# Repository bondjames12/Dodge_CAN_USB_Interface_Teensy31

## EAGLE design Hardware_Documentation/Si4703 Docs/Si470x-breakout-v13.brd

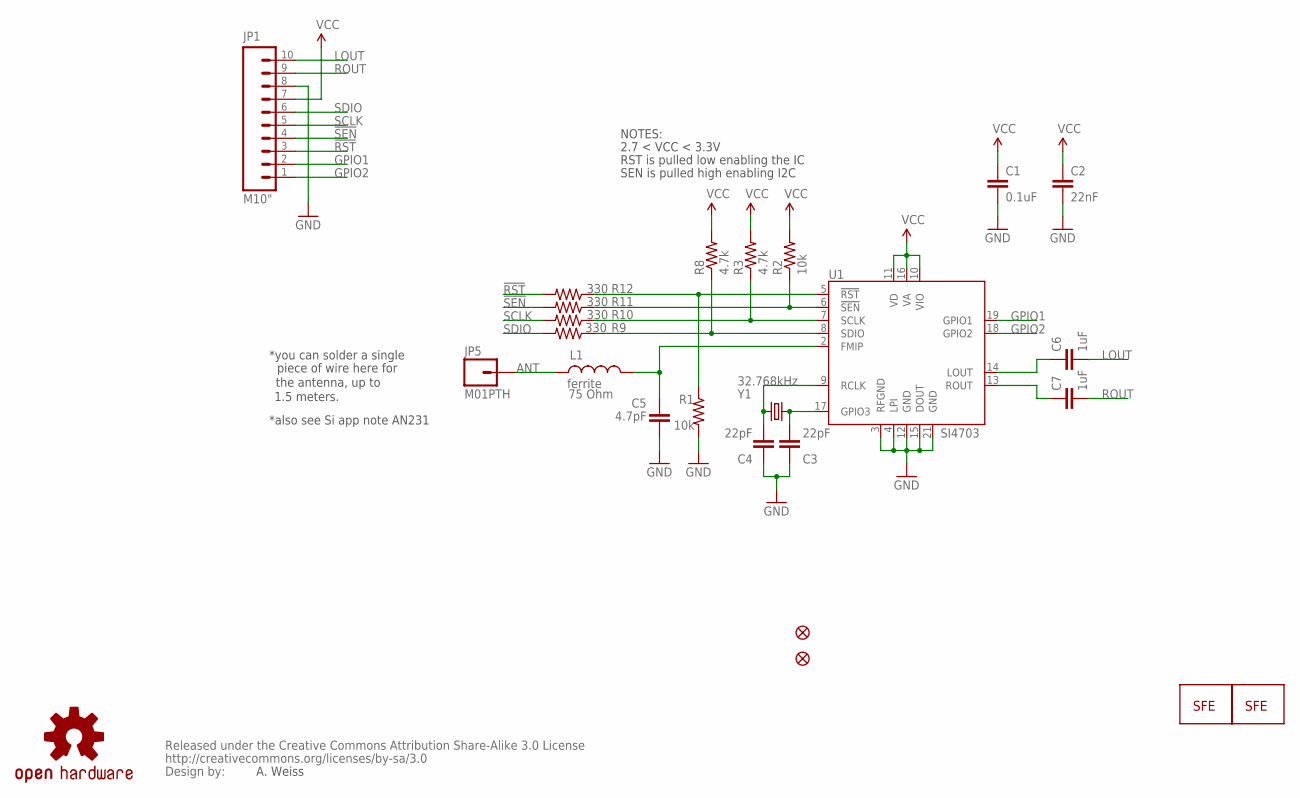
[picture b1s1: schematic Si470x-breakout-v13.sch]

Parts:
C1: 0.1uF; 0402-CAP
C2: 22nF; 0402-CAP
C3, C4: 22pF; 0402-CAP
C5: 4.7pF; 0402-CAP
C6, C7: 1uF; 0402-CAP
JP1: M10"; 1X10
JP2: LOGO-SFENW2; SFE-NEW-WEB
JP3: LOGO-SFESK; SFE-LOGO-FLAME
JP4, JP6: FIDUCIALUFIDUCIAL; MICRO-FIDUCIAL
JP5: M01PTH; 1X01
L1: ferrite; C0402
R1, R2: 10k; 0402-RES
R3, R8: 4.7k; 0402-RES
R9, R10, R11, R12: 330; 0402-RES
U1: SI4703; SPARKFUN_SI470X
U$1: CREATIVE_COMMONS
U$3: OSHW-LOGOS; OSHW-LOGO-S
Y1: 32.768kHz; CRYSTAL-32KHZ-SMD

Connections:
3.3V: C1.1, C2.1, JP1.7, R2.2, R3.2, R8.2, U1.10 (VIO), U1.11 (VD), U1.16 (VA)
!RST: JP1.3, R12.2
!RST-L: R1.1, R12.1, U1.5 (!RST)
!SEN: JP1.4, R11.2
!SEN-L: R2.1, R11.1, U1.6 (!SEN)
ANT: JP5.1, L1.1
GND: C1.2, C2.2, C3.1, C4.1, C5.2, JP1.8, R1.2, U1.3 (RFGND), U1.4 (LPI), U1.12 (GND), U1.15 (DOUT), U1.21 (GND)
GPIO1: JP1.2, U1.19 (GPIO1)
GPIO2: JP1.1, U1.18 (GPIO2)
LOUT: C6.2, JP1.10
unnamed: C4.2, U1.9 (RCLK), Y1.X2 (2)
unnamed: C3.2, U1.17 (GPIO3), Y1.X1 (1)
unnamed: C5.1, L1.2, U1.2 (FMIP)
unnamed: C6.1, U1.14 (LOUT)
unnamed: C7.1, U1.13 (ROUT)
ROUT: C7.2, JP1.9
SCLK: JP1.5, R10.2
SCLK-L: R3.1, R10.1, U1.7 (SCLK)
SDIO: JP1.6, R9.2
SDIO-L: R8.1, R9.1, U1.8 (SDIO)

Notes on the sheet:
SEN is pulled high enabling I2C
RST is pulled low enabling the IC
A. Weiss
2.7 < VCC < 3.3V
NOTES:
*you can solder a single
piece of wire here for
the antenna, up to
1.5 meters.
*also see Si app note AN231

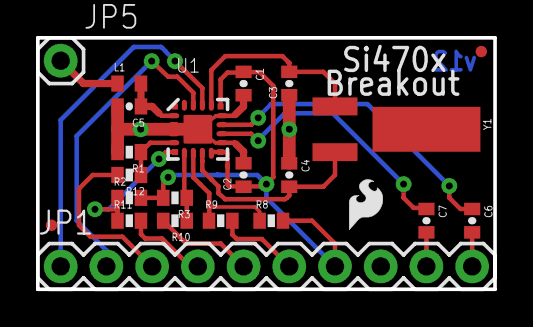
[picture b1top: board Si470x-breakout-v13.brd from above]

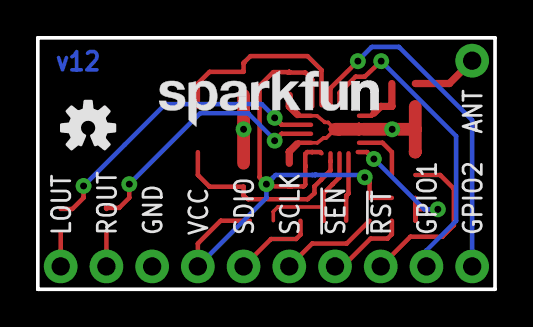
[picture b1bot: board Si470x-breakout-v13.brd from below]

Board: 2 copper layers, 25.4 x 14.0 mm, 26 parts (2 on the bottom side), 20 nets.

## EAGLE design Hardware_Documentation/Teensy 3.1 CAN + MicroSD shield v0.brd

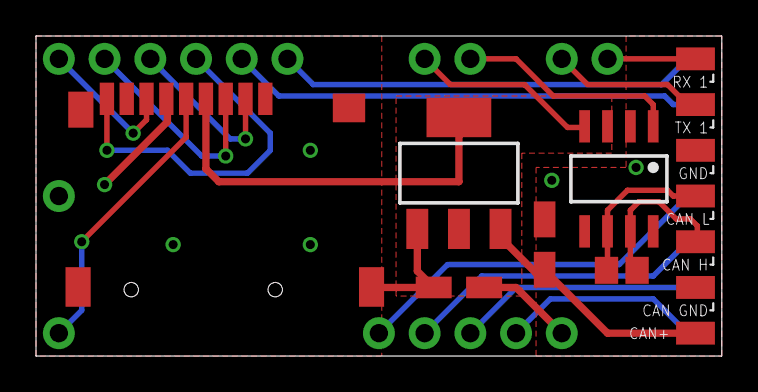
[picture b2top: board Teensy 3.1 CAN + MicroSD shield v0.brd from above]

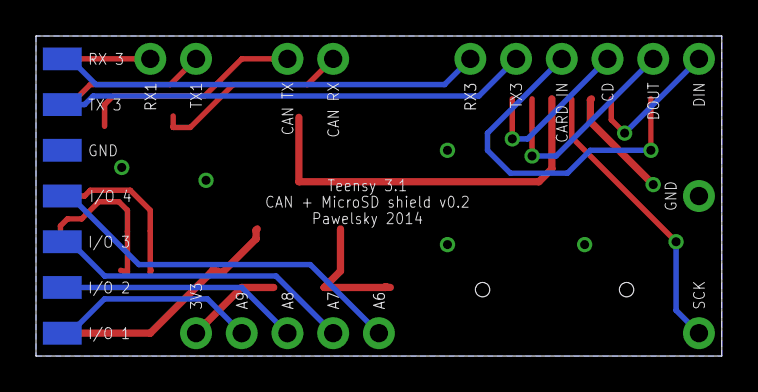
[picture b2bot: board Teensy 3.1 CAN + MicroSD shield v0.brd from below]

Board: 2 copper layers, 38.1 x 17.8 mm, 37 parts (7 on the bottom side), 20 nets.

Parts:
3V3: 3V3; 1X01-CLEANBIG
A6: A6; 1X01-CLEANBIG
A7: A7; 1X01-CLEANBIG
A8: A8; 1X01-CLEANBIG
A9: A9; 1X01-CLEANBIG
C1, C2: 10uF; CT3216
CAN+: CAN+; 1X01-SMT
CANH: CAN H; 1X01-SMT
CANL: CAN L; 1X01-SMT
CANRX: CAN RX; 1X01-CLEANBIG
CANTX: CAN TX; 1X01-CLEANBIG
CARD_IN: CARD IN; 1X01-CLEANBIG
CD: CD; 1X01-CLEANBIG
DA1: SN65HVD232; SO08
DA2: LM1117IMP-3.3; SOT223
DIN: DIN; 1X01-CLEANBIG
DOUT: DOUT; 1X01-CLEANBIG
GND: GND; 1X01-CLEANBIG
GND@2: CAN GND ^; 1X01-SMT
GND@3: GND 3; 1X01-SMT
GND@4: GND 1; 1X01-SMT
IO1: I/O 1; 1X01-SMT
IO2: I/O 2; 1X01-SMT
IO3: I/O 3; 1X01-SMT
IO4: I/O 4; 1X01-SMT
R1: 120ohm; R0805
RX1: RX1; 1X01-CLEANBIG
RX1H: RX 1; 1X01-SMT
RX3: RX3; 1X01-CLEANBIG
RX3H: RX 3; 1X01-SMT
SCK: SCK; 1X01-CLEANBIG
TX1: TX1; 1X01-CLEANBIG
TX1H: TX 1; 1X01-SMT
TX3: TX3; 1X01-CLEANBIG
TX3H: TX 3; 1X01-SMT
U$1: MICROSD_PP

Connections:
3V3: 3V3.1, C2.+, DA1.3, DA2.2, DA2.4, U$1.4
CAN+: C1.+, CAN+.1, DA2.3
CANH: CANH.1, DA1.7, R1.1
CANL: CANL.1, DA1.6, R1.2
CANRX: CANRX.1, DA1.4
CANTX: CANTX.1, DA1.1
CARD_IN: CARD_IN.1, U$1.9
CS: CD.1, U$1.2
GND: C1.-, C2.-, DA1.2, DA1.8, DA2.1, GND.1, GND@2.1, GND@3.1, GND@4.1, U$1.6, U$1.GND@1, U$1.GND@2, U$1.GND@3, U$1.GND@4
MISO: DIN.1, U$1.7
MOSI: DOUT.1, U$1.3
unnamed: TX3.1, TX3H.1
unnamed: TX1.1, TX1H.1
unnamed: RX3.1, RX3H.1
unnamed: RX1.1, RX1H.1
unnamed: A9.1, IO1.1
unnamed: A8.1, IO2.1
unnamed: A7.1, IO3.1
unnamed: A6.1, IO4.1
SCK: SCK.1, U$1.5

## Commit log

2015-07-15 Working Version 1. CAN receiver and send features = complete. USB HID Communication for CAN = complete Dodge radio emulator and radio CAN message decoding = complete
2015-07-15 Add Hardware Documentation files and examples
2015-07-15 Add CANLogger class to log CAN data to SD Card using Arduino SD library
2015-07-15 Remove LED pin 13 code from radioEmulator Class. Pin 13 is now used for SD Card communication (SPI)
2015-07-15 Add Si4703 FM Radio control code. Added Teensy Pin usage notes
2015-07-15 Eclipse pref update
2015-08-16 Add FM Radio Status (RSSI, Stereo, channel update) Add FM Radio Power methods
2015-08-29 Move FM radio volume settings
2015-12-31 Hardcode initial volume, balance, fade,bass,mid, and treble start up values instead of using EEPROM
2016-02-13 Update config add hardware schmatic
2016-03-23 Remove unneed Sirius radio function
2019-02-26 Working encoders (left and right side) working FM radio (a bit slow but works)

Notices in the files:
parts and their libraries:
SparkFun-Passives: Licensing: CC v3.0 Share-Alike You are welcome to use this library for commercial purposes.
SparkFun-Aesthetics: Released under the Creative Commons Attribution Share-Alike 3.0 License
SparkFun-Aesthetics: http://creativecommons.org/licenses/by-sa/3.0
